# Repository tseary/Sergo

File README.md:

# Sergo
Sergo is a custom circuit board I made to interface hobby servos (or Geek servos) with Lego Power Functions. It has an ATTINY84 microcontroller and a 5 V, 2.5 A buck converter. It supports up to two servos, and can be controlled either from a PF receiver or directly by IR remote. It is programmed in Arduino.

# Make Your Own
Disclaimer: This is not a how-to guide. I have shared this project for general interest and in case the source code is useful to anyone. However, if you want to make your own Sergo, I am assuming you already have some knowledge of surface-mount soldering. You will need reflow soldering materials and equipment. **This project _cannot_ be assembled with only a soldering iron!**

## Gather Parts
The bare PCB without components can be ordered from [OSH Park](https://oshpark.com/shared_projects/rSyxp330).

Here is a [Digikey cart](https://www.digikey.ca/short/tn3525p4) with all of the components. The cost of parts for one board is about $15.61 CAD (or $13.92 CAD if the IR receiver is omitted).

It is recommended to apply solder paste to the board with a stencil. I used a polyimide film stencil of 0.005" thickness from [OSH Stencils](https://www.oshstencils.com). The stencil gerber file is "KiCad/gerbers/Sergo-F_Paste.gbr". Alternatively, solder paste may be applied freehand with a syringe. Particular care should be taken to apply the paste neatly under the buck converter PS1.

## Assembly, Programming, and Testing
More details to come...

# Show Me!
If you do attempt to build this project, I'd like to see it! Find me on [Eurobricks](https://www.eurobricks.com/forum/index.php?/profile/207750-tseary/).

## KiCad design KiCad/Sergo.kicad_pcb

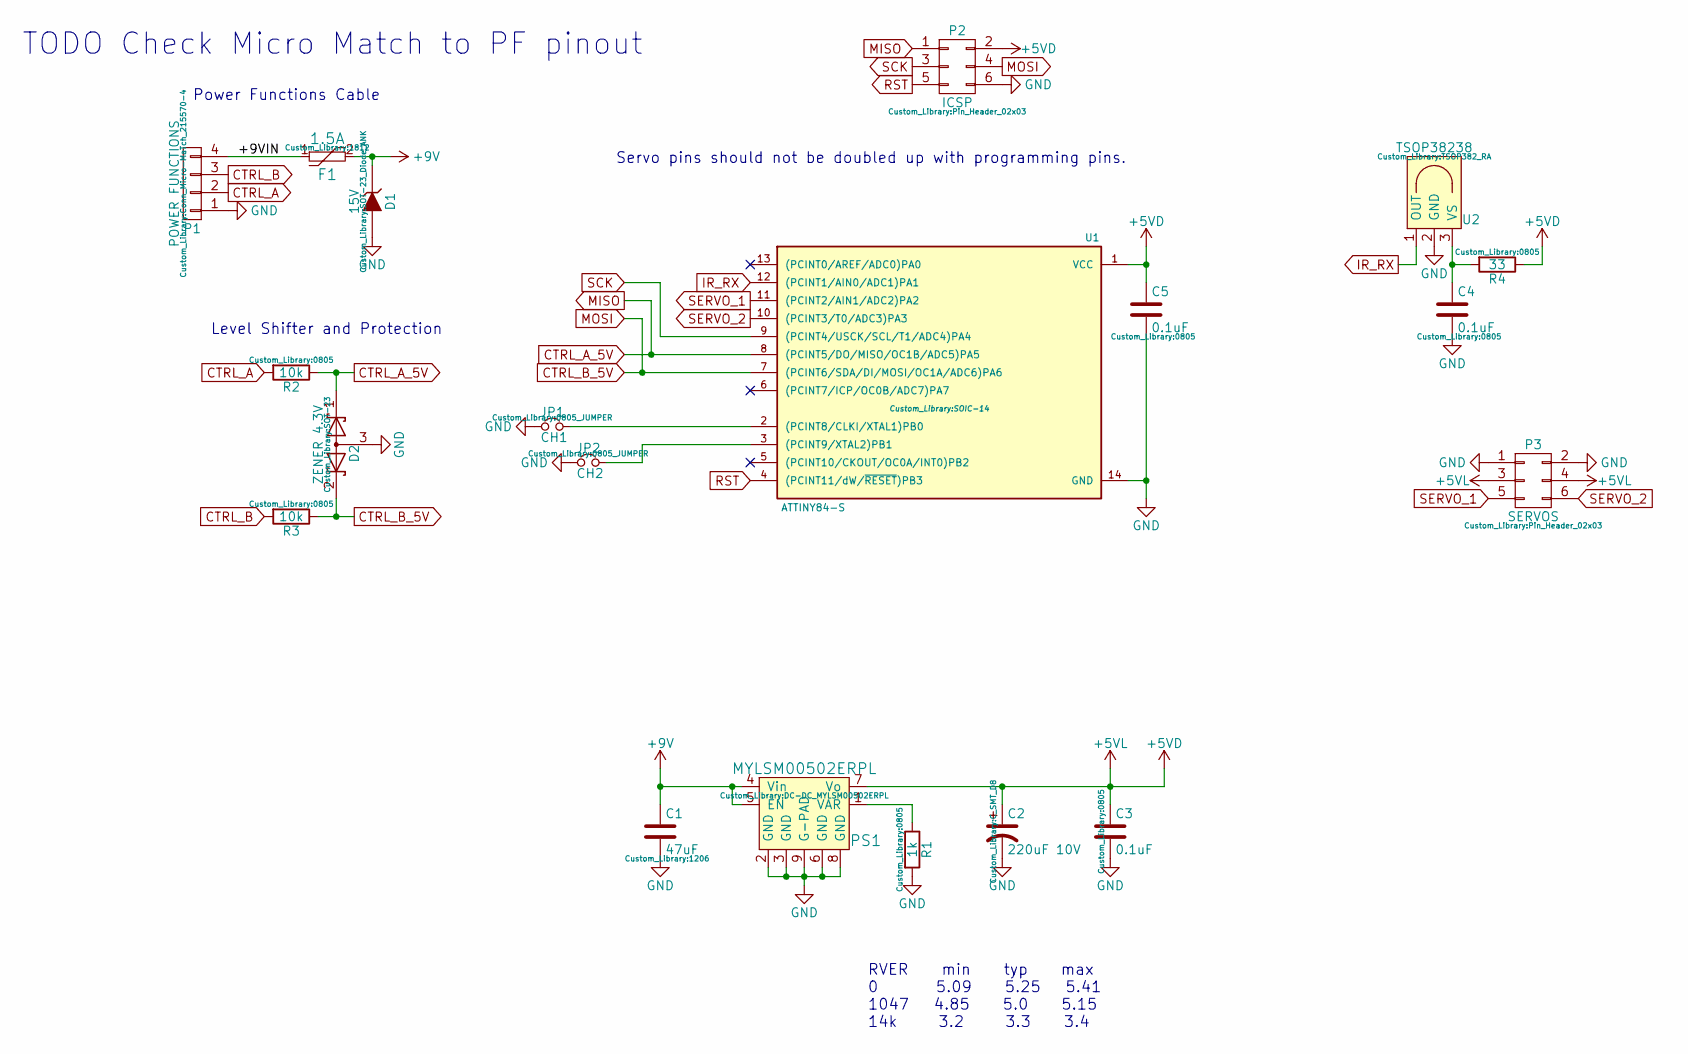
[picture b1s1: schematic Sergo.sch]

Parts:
C1: 47uF; 1206
C2: 220uF 10V; C_SMT_D8
C3, C4, C5: 0.1uF; 0805
D1: 15V; SOT-23_Diode_ANK
D2: ZENER 4.3V; SOT-23
F1: 1.5A; 1812
JP1: CH1; 0805_JUMPER
JP2: CH2; 0805_JUMPER
P1: POWER FUNCTIONS; Conn_Micro-MaTch_215570-4
P2: ICSP; Pin_Header_02x03
P3: SERVOS; Pin_Header_02x03
PS1: MYLSM00502ERPL; DC-DC_MYLSM00502ERPL
R1: 1k; 0805
R2, R3: 10k; 0805
R4: 33; 0805
U1: ATTINY84-S; SOIC-14
U2: TSOP38238; TSOP382_RA

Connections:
+5VD: C2.1, C3.1, C5.1, P2.2, P3.3, P3.4, PS1.7 (Vo), R4.1, U1.1 (VCC)
+9V: C1.1, D1.1 (K), F1.2, PS1.4 (Vin), PS1.5 (EN)
/+9VIN: F1.1, P1.4
CTRL_A: P1.2, R2.2
CTRL_B: P1.3, R3.2
CTRL_B_5V: D2.2 (K), P2.4, R3.1, U1.7 ((PCINT6/SDA/DI/MOSI/OC1A/ADC6)PA6)
GND: C1.2, C2.2, C3.2, C4.2, C5.2, D1.2 (A), D2.3 (A), JP1.1, JP2.1, P1.1, P2.6, P3.1, P3.2, PS1.2 (GND), PS1.3 (GND), PS1.6 (GND), PS1.8 (GND), PS1.9 (G-PAD), R1.2, U1.14 (GND), U2.2 (GND)
IR_RX: U1.12 ((PCINT1/AIN0/ADC1)PA1), U2.1 (OUT)
MISO: D2.1 (K), P2.1, R2.1, U1.8 ((PCINT5/DO/MISO/OC1B/ADC5)PA5)
unnamed: C4.1, R4.2, U2.3 (VS)
unnamed: JP1.2, U1.2 ((PCINT8/CLKI/XTAL1)PB0)
unnamed: JP2.2, U1.3 ((PCINT9/XTAL2)PB1)
unnamed: PS1.1 (VAR), R1.1
RST: P2.5, U1.4 ((PCINT11/dW/~RESET~)PB3)
SCK: P2.3, U1.9 ((PCINT4/USCK/SCL/T1/ADC4)PA4)
SERVO_1: P3.5, U1.11 ((PCINT2/AIN1/ADC2)PA2)
SERVO_2: P3.6, U1.10 ((PCINT3/T0/ADC3)PA3)

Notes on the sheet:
RVER min typ max 0 5.09 5.25 5.41 1047 4.85 5.0 5.15 14k 3.2 3.3 3.4
Level Shifter and Protection
Power Functions Cable
Servo pins should not be doubled up with programming pins.
TODO Check Micro Match to PF pinout

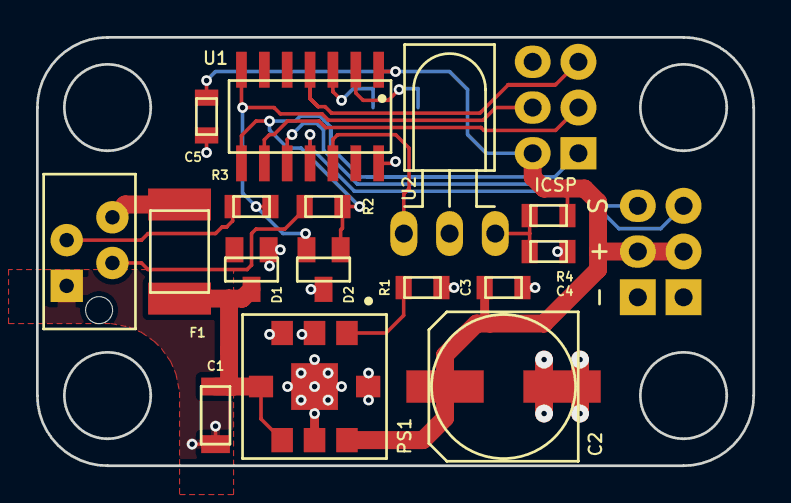
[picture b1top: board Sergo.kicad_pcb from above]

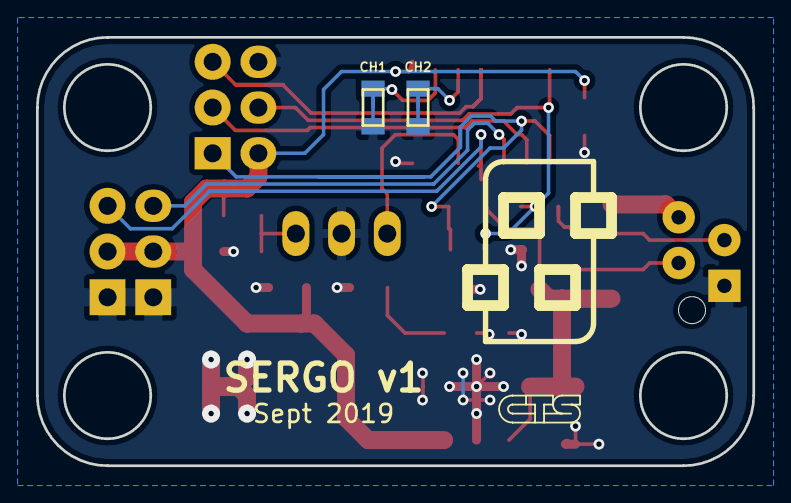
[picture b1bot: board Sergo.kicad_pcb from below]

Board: 2 copper layers, 39.8 x 23.8 mm, 20 parts (2 on the bottom side), 17 nets.

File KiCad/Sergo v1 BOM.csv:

"Id";"Designator";"Package";"Quantity";"Designation";"Supplier and ref";
1;"C1";"1206";1;"47uF";;;
2;"C4,C5,C3";"0805";3;"0.1uF";;;
3;"P2";"Pin_Header_02x03";1;"ICSP";;;
4;"P3";"Pin_Header_02x03";1;"SERVOS";;;
5;"U2";"TSOP382_RA";1;"TSOP38238";;;
6;"C2";"C_SMT_D8";1;"220uF 10V";;;
7;"R2,R3";"0805";2;"10k";;;
8;"R4";"0805";1;"33";;;
9;"PS1";"DC-DC_MYLSM00502ERPL";1;"MYLSM00502ERPL";;;
10;"P1";"Conn_Micro-MaTch_215570-4";1;"POWER FUNCTIONS";;;
11;"F1";"1812";1;"1.5A";;;
12;"D1";"SOT-23_Diode_ANK";1;"15V";;;
13;"D2";"SOT-23";1;"ZENER 4.3V";;;
14;"U1";"SOIC-14";1;"ATTINY84-S";;;
15;"R1";"0805";1;"1k";;;
16;"JP2";"0805_JUMPER";1;"CH2";;;
17;"JP1";"0805_JUMPER";1;"CH1";;;

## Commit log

2019-09-21 A bunch of garbage
2019-09-21 Added test code for ATMEGA328P
    Proof of concept, receiving PF IR commands and controlling a servo.
2019-09-22 Adjusted servo center
2019-09-22 Port from ATMEGA328P to ATTINY84
    Removed 328-specific functionality. Updated interrupts for ATTINY84. Now using modified SoftServo library instead of normal Servo library.
2019-09-22 Moved Code from IR_Test_3 to SergoController
    Added local library SoftServoLowLatency.
2019-09-22 Check channel before checksum
2019-09-22 Second servo
    Added second servo and changed servo pin numbers. Fixed lost communication timeout.
2019-09-25 Swap pins
    Swapped RX and servo B pins to improve PCB layout.
2020-01-02 Added C1 C2 control
    Added basic support for PF receiver.
2024-11-08 Add KiCad project
    Here is the KiCad project for the PCB, as ordered.
